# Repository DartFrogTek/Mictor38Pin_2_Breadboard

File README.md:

# Mictor 38Pin to Breadboard
A Mictor 38 Pin to Breadboard adapter. Allows Mictor connectors for high end Logic Analyzers to interface with breadboard and/or prototype PCBs.

Renders show dual Male Pin Headers on the top in all spaces. Instead you can place a Female Socket or a set of Male Pins. I would place male pins on bottom side in J2/J5/J4 and solder from top. You can either leave J3/J6/J7 empty or you can add male pins or female sockets to the top if desired. J2/J6 are connected. J4/J7 are connected. J5/J3 are connected.

Order from PCBWay with my shared project!
https://www.pcbway.com/project/shareproject/Mictor_38Pin_Logic_Analyzer_Probe_Breakout_98119768.html

### Female Mictor 38 Pin Connector
- TE Connectivity AMP Connectors [5767061-1](https://www.digikey.com/en/products/detail/te-connectivity-amp-connectors/5767061-1/2195045)
- TE Connectivity AMP Connectors [2-5767004-2](https://www.futureelectronics.com/p/interconnect--dual-in-line-package-sockets/2-5767004-2-te-connectivity-7561798)
  
Both work. (5767061-1) and (2-5767004-2) are identical except:
  - (2-5767004-2)'s 5 through-hole ground pins are slightly under flush with the surface of a 1.6mm FR4 board.
  - (5767061-1)'s 5 through-hole ground pins protrude above by 2.00mm of the surface of a 1.6mm FR4 board.

### Renders

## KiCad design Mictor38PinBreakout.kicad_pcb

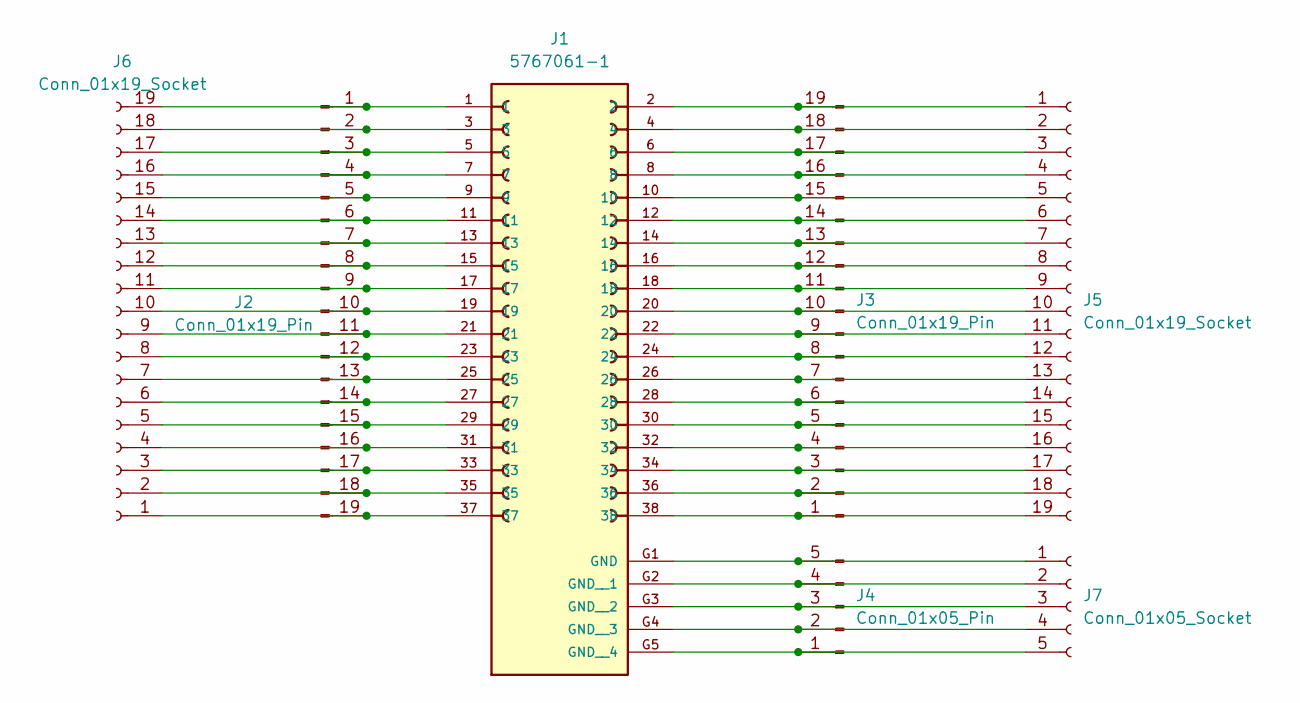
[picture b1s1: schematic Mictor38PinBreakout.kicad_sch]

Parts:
J1: 5767061-1; TE_5767061-1; PARTREV B1
J2, J3: Conn_01x19_Pin; PinHeader_1x19_P2.54mm_Vertical
J4: Conn_01x05_Pin; PinHeader_1x05_P2.54mm_Vertical
J5, J6: Conn_01x19_Socket; PinHeader_1x19_P2.54mm_Vertical
J7: Conn_01x05_Socket; PinHeader_1x05_P2.54mm_Vertical

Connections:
unnamed: J1.G1 (GND), J4.5, J7.1
unnamed: J1.G2 (GND__1), J4.4, J7.2
unnamed: J1.G3 (GND__2), J4.3, J7.3
unnamed: J1.G4 (GND__3), J4.2, J7.4
unnamed: J1.G5 (GND__4), J4.1, J7.5
unnamed: J1.1, J2.1, J6.19
unnamed: J1.3, J2.2, J6.18
unnamed: J1.5, J2.3, J6.17
unnamed: J1.7, J2.4, J6.16
unnamed: J1.9, J2.5, J6.15
unnamed: J1.11, J2.6, J6.14
unnamed: J1.13, J2.7, J6.13
unnamed: J1.15, J2.8, J6.12
unnamed: J1.17, J2.9, J6.11
unnamed: J1.19, J2.10, J6.10
unnamed: J1.21, J2.11, J6.9
unnamed: J1.23, J2.12, J6.8
unnamed: J1.25, J2.13, J6.7
unnamed: J1.27, J2.14, J6.6
unnamed: J1.29, J2.15, J6.5
unnamed: J1.31, J2.16, J6.4
unnamed: J1.33, J2.17, J6.3
unnamed: J1.35, J2.18, J6.2
unnamed: J1.37, J2.19, J6.1
unnamed: J1.38, J3.1, J5.19
unnamed: J1.36, J3.2, J5.18
unnamed: J1.34, J3.3, J5.17
unnamed: J1.32, J3.4, J5.16
unnamed: J1.30, J3.5, J5.15
unnamed: J1.28, J3.6, J5.14
unnamed: J1.26, J3.7, J5.13
unnamed: J1.24, J3.8, J5.12
unnamed: J1.22, J3.9, J5.11
unnamed: J1.20, J3.10, J5.10
unnamed: J1.18, J3.11, J5.9
unnamed: J1.16, J3.12, J5.8
unnamed: J1.14, J3.13, J5.7
unnamed: J1.12, J3.14, J5.6
unnamed: J1.10, J3.15, J5.5
unnamed: J1.8, J3.16, J5.4
unnamed: J1.6, J3.17, J5.3
unnamed: J1.4, J3.18, J5.2
unnamed: J1.2, J3.19, J5.1

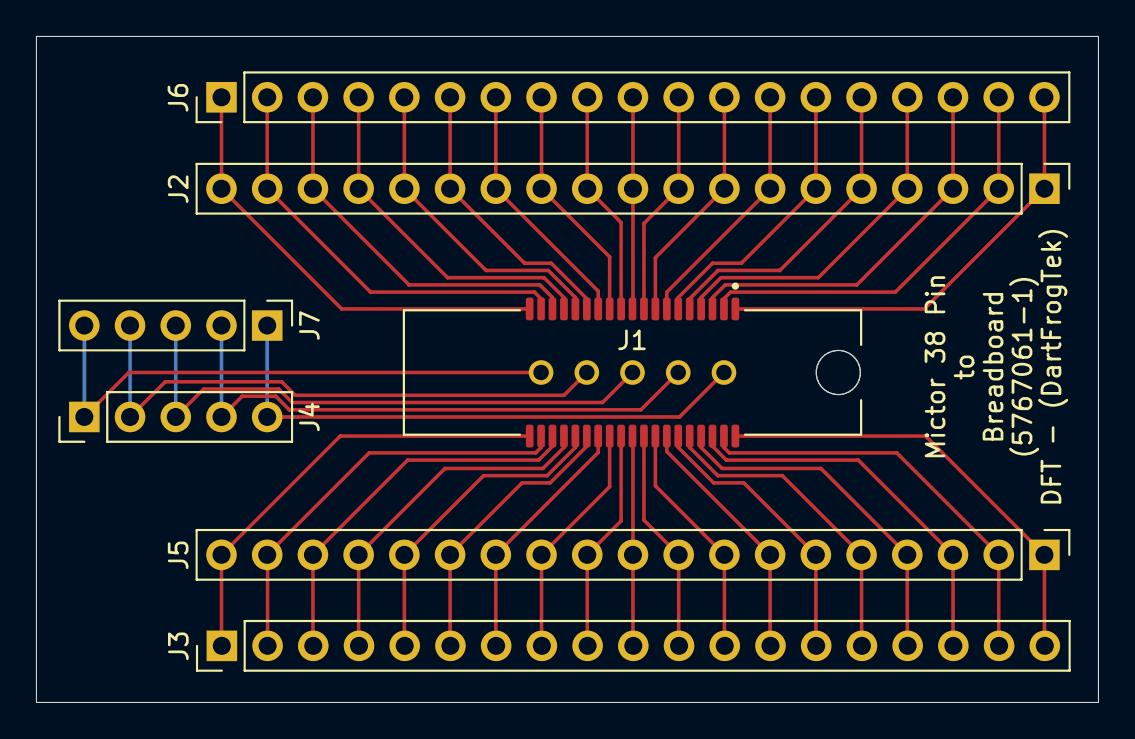
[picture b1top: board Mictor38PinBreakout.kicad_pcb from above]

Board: 2 copper layers, 59.0 x 37.0 mm, 7 parts (0 on the bottom side), 43 nets.

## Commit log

2025-05-04 Initial Commit.
2025-05-31 Add another part number
